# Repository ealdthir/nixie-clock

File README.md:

View this project on [CADLAB.io](https://cadlab.io/project/1190). 

# nixie-clock

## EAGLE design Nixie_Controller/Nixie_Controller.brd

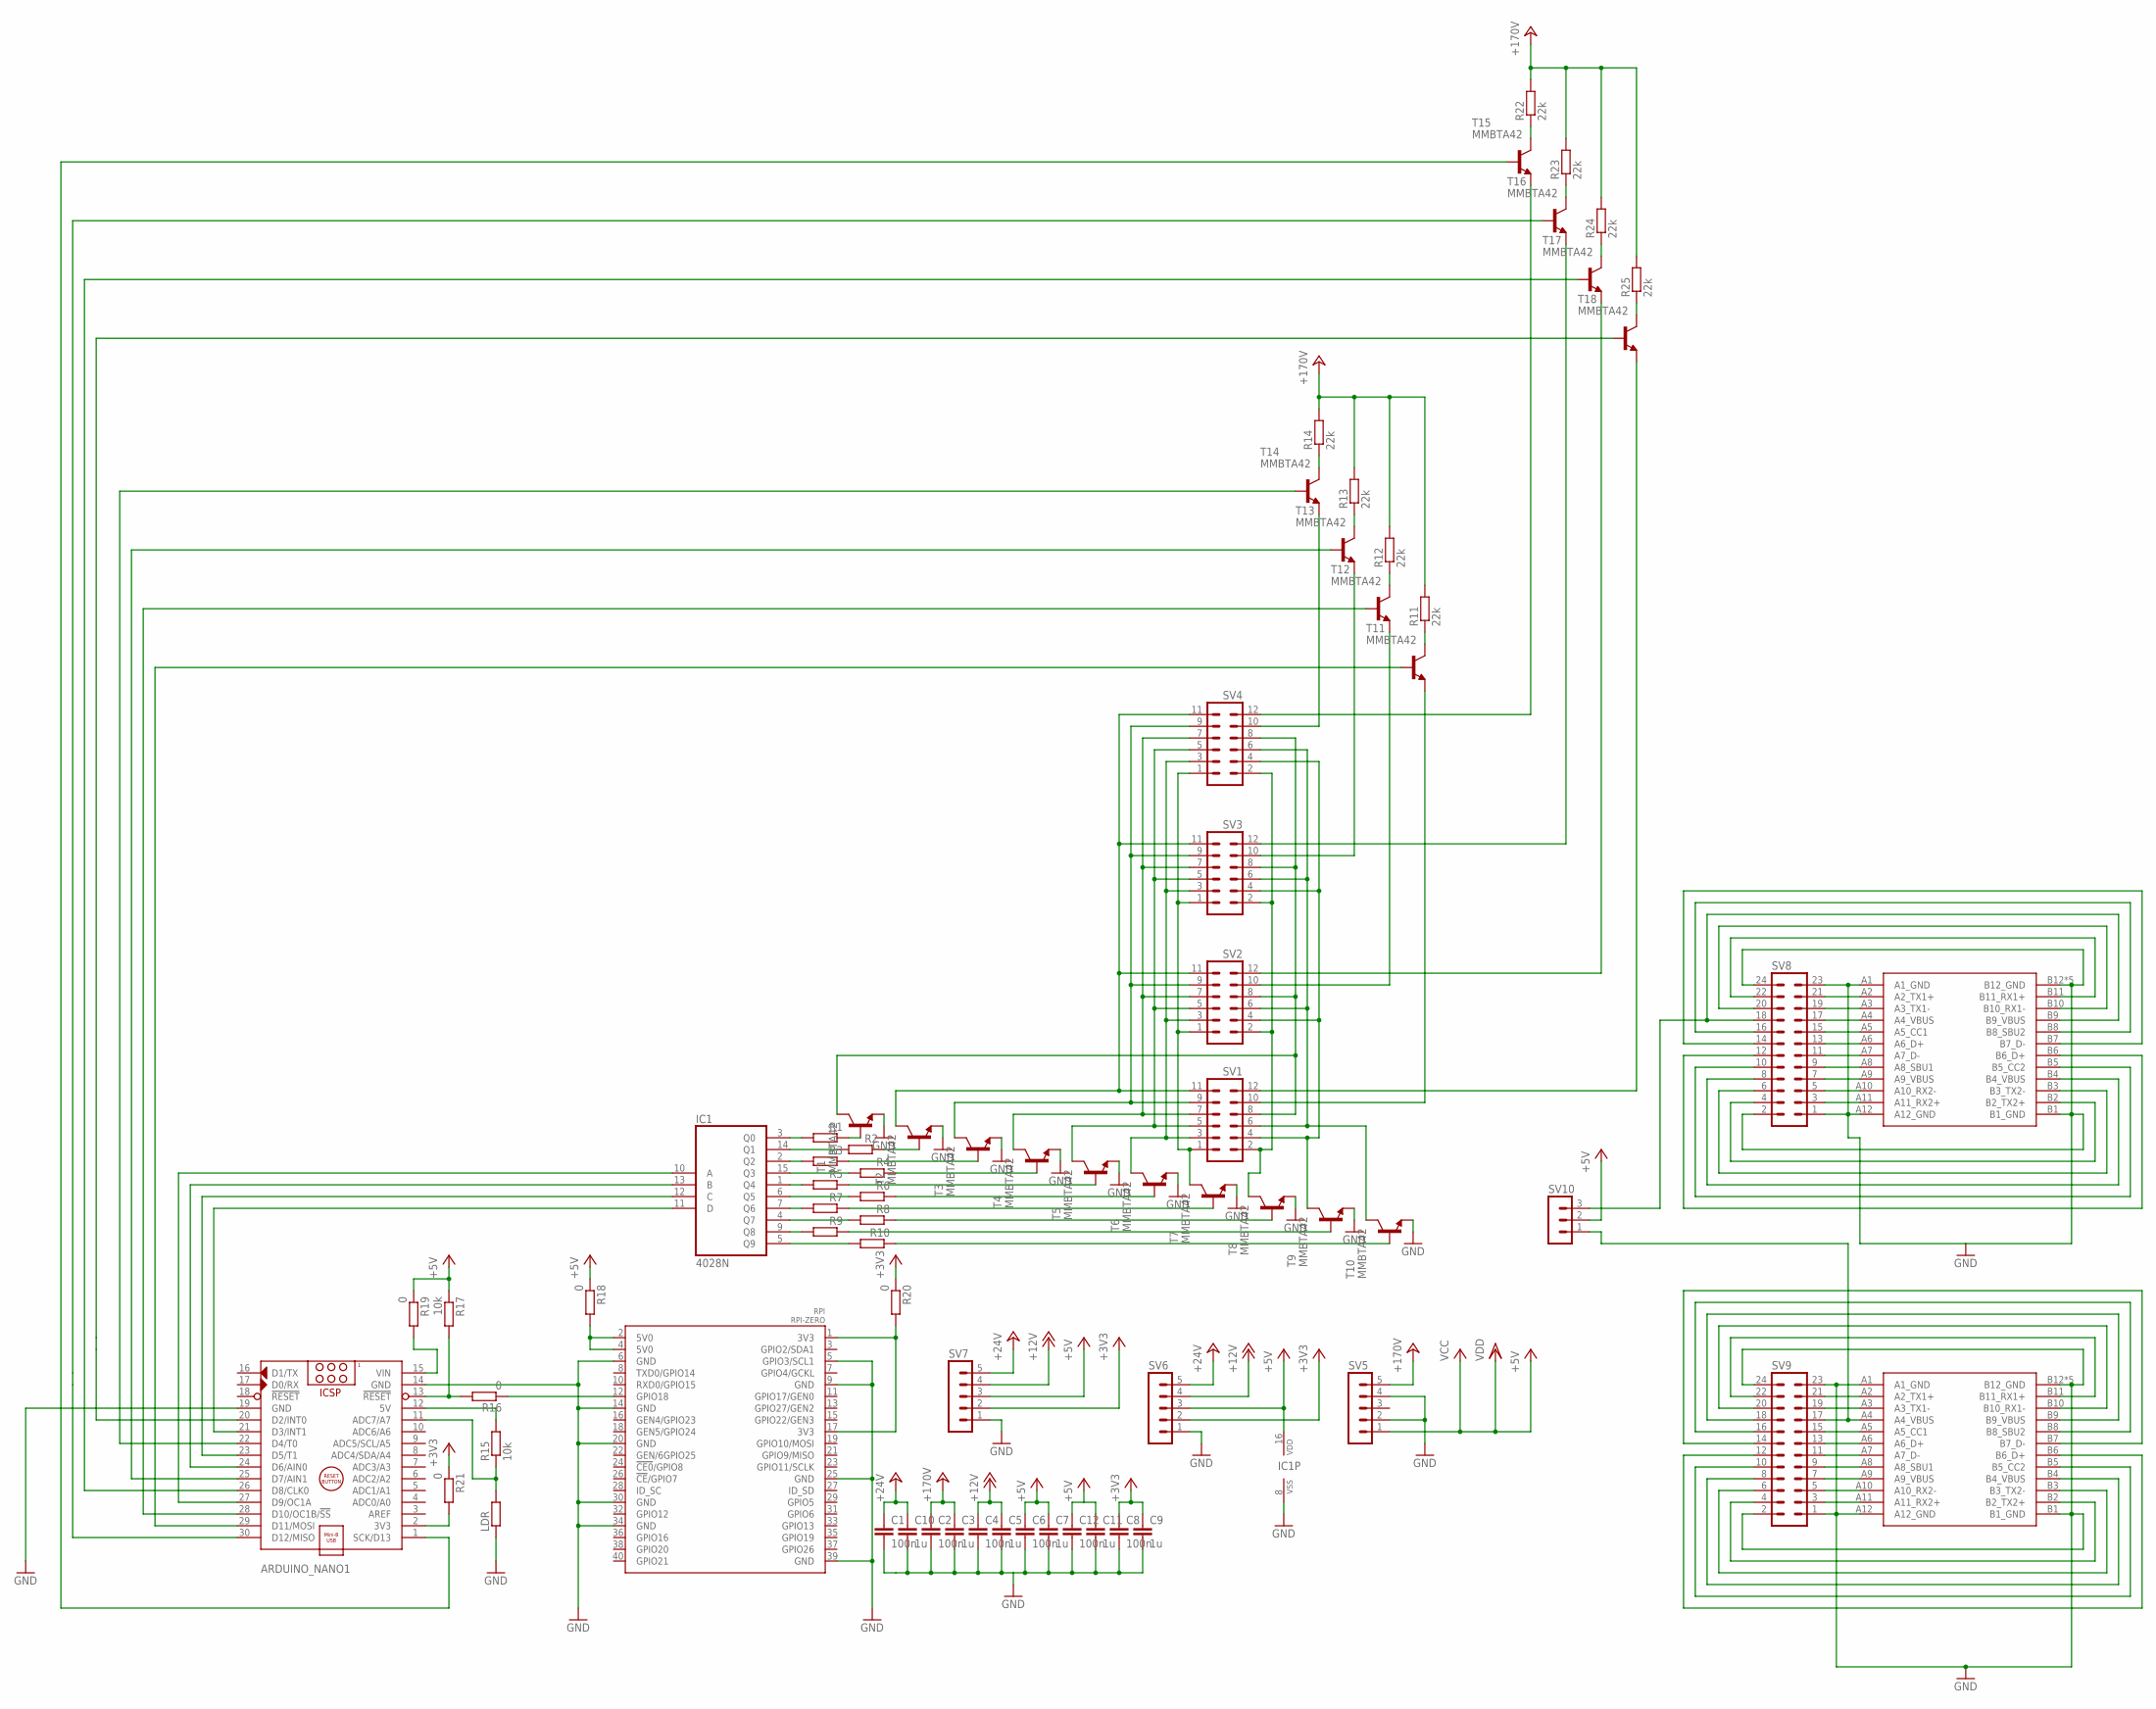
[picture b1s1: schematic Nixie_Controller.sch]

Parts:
ARDUINO_NANO1: ARDUINO_NANO
C1, C2, C4, C6, C8, C12: 100n; C0805
C3, C5, C7, C9, C10, C11: 1u; C0805
IC1: 4028N; DIL16
LDR: R-EU_0204/7; 0204/7
R1, R2, R3, R4, R5, R6, R7, R8, R9, R10: R-EU_R0603; R0603
R11, R12, R13, R14, R22, R23, R24, R25: 22k; R0603
R15, R17: 10k; R0603
R16, R18, R19, R20, R21: 0; R0603
RPI: RPI-ZERO; RASP_PI_ZERO_BOARD_FULL
SV1, SV2, SV3, SV4: MA06-2
SV5, SV6, SV7: MA05-1
SV8, SV9: MA12-2
SV10: MA03-1
T1, T2, T3, T4, T5, T6, T7, T8, T9, T10, T11, T12, T13, T14, T15, T16, T17, T18: MMBTA42; SOT23
USBC1, USBC2: USB-TYPE-C

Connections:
3V3@2: R20.2, RPI.1 (3V3), RPI.17 (3V3)
+3V3: C8.1, C9.1, R20.1, R21.1, SV6.2, SV7.2
+5V: R18.2, RPI.2 (5V0), RPI.4 (5V0)
+12V: C4.1, C5.1, SV6.4, SV7.4
+24V: C1.1, C10.1, SV6.5, SV7.5
+170V: C2.1, C3.1, R11.2, R12.2, R13.2, R14.2, R22.2, R23.2, R24.2, R25.2, SV5.5
GND: ARDUINO_NANO1.14 (GND), ARDUINO_NANO1.19 (GND), C1.2, C2.2, C3.2, C4.2, C5.2, C6.2, C7.2, C8.2, C9.2, C10.2, C11.2, C12.2, IC1.8 (VSS), LDR.1, RPI.5 (GPIO3/SCL1), RPI.6 (GND), RPI.9 (GND), RPI.14 (GND), RPI.20 (GND), RPI.25 (GND), RPI.30 (GND), RPI.34 (GND), RPI.39 (GND), SV5.2, SV5.4, SV6.1, SV7.1, SV8.1, SV8.2, SV8.23, SV8.24, SV9.1, SV9.2, SV9.23, SV9.24, T1.2 (E), T2.2 (E), T3.2 (E), T4.2 (E), T5.2 (E), T6.2 (E), T7.2 (E), T8.2 (E), T9.2 (E), T10.2 (E), USBC1.A1 (A1_GND), USBC1.A12 (A12_GND), USBC1.B1 (B1_GND), USBC1.B12 (B12_GND), USBC1.C1 (B12_GND), USBC1.C2 (B12_GND), USBC1.C3 (B12_GND), USBC1.C4 (B12_GND), USBC2.A1 (A1_GND), USBC2.A12 (A12_GND), USBC2.B1 (B1_GND), USBC2.B12 (B12_GND), USBC2.C1 (B12_GND), USBC2.C2 (B12_GND), USBC2.C3 (B12_GND), USBC2.C4 (B12_GND)
unnamed: IC1.3 (Q0), R1.2
unnamed: IC1.14 (Q1), R2.2
unnamed: IC1.2 (Q2), R3.2
unnamed: IC1.15 (Q3), R4.2
unnamed: IC1.1 (Q4), R5.2
unnamed: IC1.6 (Q5), R6.2
unnamed: IC1.7 (Q6), R7.2
unnamed: IC1.4 (Q7), R8.2
unnamed: IC1.9 (Q8), R9.2
unnamed: IC1.5 (Q9), R10.2
unnamed: R1.1, T1.1 (B)
unnamed: R2.1, T2.1 (B)
unnamed: R3.1, T3.1 (B)
unnamed: R4.1, T4.1 (B)
unnamed: R6.1, T6.1 (B)
unnamed: R5.1, T5.1 (B)
unnamed: R7.1, T7.1 (B)
unnamed: R8.1, T8.1 (B)
unnamed: R10.1, T10.1 (B)
unnamed: R9.1, T9.1 (B)
unnamed: SV1.11, SV2.11, SV3.11, SV4.11, T2.3 (C)
unnamed: SV1.9, SV2.9, SV3.9, SV4.9, T3.3 (C)
unnamed: SV1.7, SV2.7, SV3.7, SV4.7, T4.3 (C)
unnamed: SV1.5, SV2.5, SV3.5, SV4.5, T5.3 (C)
unnamed: SV1.3, SV2.3, SV3.3, SV4.3, T6.3 (C)
unnamed: SV1.1, SV2.1, SV3.1, SV4.1, T7.3 (C)
unnamed: SV1.2, SV2.2, SV3.2, SV4.2, T8.3 (C)
unnamed: SV1.4, SV2.4, SV3.4, SV4.4, T9.3 (C)
unnamed: SV1.6, SV2.6, SV3.6, SV4.6, T10.3 (C)
unnamed: SV1.8, SV2.8, SV3.8, SV4.8, T1.3 (C)
unnamed: R14.1, T14.3 (C)
unnamed: R11.1, T11.3 (C)
unnamed: R12.1, T12.3 (C)
unnamed: R13.1, T13.3 (C)
unnamed: SV4.10, T14.2 (E)
unnamed: SV3.10, T13.2 (E)
unnamed: SV2.10, T12.2 (E)
unnamed: SV1.10, T11.2 (E)
unnamed: ARDUINO_NANO1.2 (3V3), R21.2
unnamed: ARDUINO_NANO1.28 (D10/OC1B/!SS), T12.1 (B)
unnamed: SV8.21, USBC2.A2 (A2_TX1+)
unnamed: SV8.19, USBC2.A3 (A3_TX1-)
unnamed: ARDUINO_NANO1.13 (!RESET), R16.2, R17.2
unnamed: ARDUINO_NANO1.12 (5V), R15.2
unnamed: ARDUINO_NANO1.11 (ADC7/A7), LDR.2, R15.1
unnamed: ARDUINO_NANO1.29 (D11/MOSI), T11.1 (B)
unnamed: SV8.17, USBC2.A4 (A4_VBUS)
unnamed: ARDUINO_NANO1.25 (D7/AIN1), T13.1 (B)
unnamed: ARDUINO_NANO1.22 (D4/T0), T14.1 (B)
unnamed: SV8.15, USBC2.A5 (A5_CC1)
unnamed: SV8.13, USBC2.A6 (A6_D+)
unnamed: SV8.11, USBC2.A7 (A7_D-)
unnamed: SV8.9, USBC2.A8 (A8_SBU1)
unnamed: SV8.7, USBC2.A9 (A9_VBUS)
unnamed: SV8.5, USBC2.A10 (A10_RX2-)
unnamed: SV8.3, USBC2.A11 (A11_RX2+)
unnamed: R22.1, T15.3 (C)
unnamed: R25.1, T18.3 (C)
unnamed: SV9.21, USBC1.A2 (A2_TX1+)
unnamed: SV9.19, USBC1.A3 (A3_TX1-)
unnamed: SV9.17, SV10.1, USBC1.A4 (A4_VBUS)
unnamed: SV9.15, USBC1.A5 (A5_CC1)
unnamed: SV9.13, USBC1.A6 (A6_D+)
unnamed: SV9.11, USBC1.A7 (A7_D-)
unnamed: SV9.9, USBC1.A8 (A8_SBU1)
unnamed: SV9.7, USBC1.A9 (A9_VBUS)
unnamed: SV9.5, USBC1.A10 (A10_RX2-)
unnamed: SV9.3, USBC1.A11 (A11_RX2+)
unnamed: R24.1, T17.3 (C)
unnamed: R23.1, T16.3 (C)
unnamed: SV9.4, USBC1.B2 (B2_TX2+)
unnamed: SV9.6, USBC1.B3 (B3_TX2-)
unnamed: SV9.8, USBC1.B4 (B4_VBUS)
unnamed: SV9.10, USBC1.B5 (B5_CC2)
unnamed: SV9.12, USBC1.B6 (B6_D+)
unnamed: SV4.12, T15.2 (E)
unnamed: SV9.22, USBC1.B11 (B11_RX1+)
unnamed: SV9.20, USBC1.B10 (B10_RX1-)
unnamed: SV9.18, USBC1.B9 (B9_VBUS)
unnamed: SV9.16, USBC1.B8 (B8_SBU2)
unnamed: SV9.14, USBC1.B7 (B7_D-)
unnamed: SV3.12, T16.2 (E)
unnamed: SV8.4, USBC2.B2 (B2_TX2+)
unnamed: SV8.6, USBC2.B3 (B3_TX2-)
unnamed: SV8.8, USBC2.B4 (B4_VBUS)
unnamed: SV8.10, USBC2.B5 (B5_CC2)
unnamed: SV8.12, USBC2.B6 (B6_D+)
unnamed: SV2.12, T17.2 (E)
unnamed: SV8.22, USBC2.B11 (B11_RX1+)
unnamed: SV8.20, USBC2.B10 (B10_RX1-)
unnamed: SV8.18, SV10.3, USBC2.B9 (B9_VBUS)
unnamed: SV8.16, USBC2.B8 (B8_SBU2)
unnamed: SV8.14, USBC2.B7 (B7_D-)
unnamed: R16.1, RPI.12 (GPIO18)
unnamed: SV1.12, T18.2 (E)
unnamed: ARDUINO_NANO1.15 (VIN), R19.2
unnamed: ARDUINO_NANO1.1 (SCK/D13), T15.1 (B)
unnamed: ARDUINO_NANO1.20 (D2/INT0), T18.1 (B)
unnamed: ARDUINO_NANO1.26 (D8/CLK0), T17.1 (B)
unnamed: ARDUINO_NANO1.30 (D12/MISO), T16.1 (B)
unnamed: ARDUINO_NANO1.21 (D3/INT1), IC1.11 (D)
unnamed: ARDUINO_NANO1.23 (D5/T1), IC1.12 (C)
unnamed: ARDUINO_NANO1.24 (D6/AIN0), IC1.13 (B)
unnamed: ARDUINO_NANO1.27 (D9/OC1A), IC1.10 (A)
VDD: C6.1, C7.1, C11.1, C12.1, IC1.16 (VDD), R17.1, R18.1, R19.1, SV5.1, SV6.3, SV7.3, SV10.2

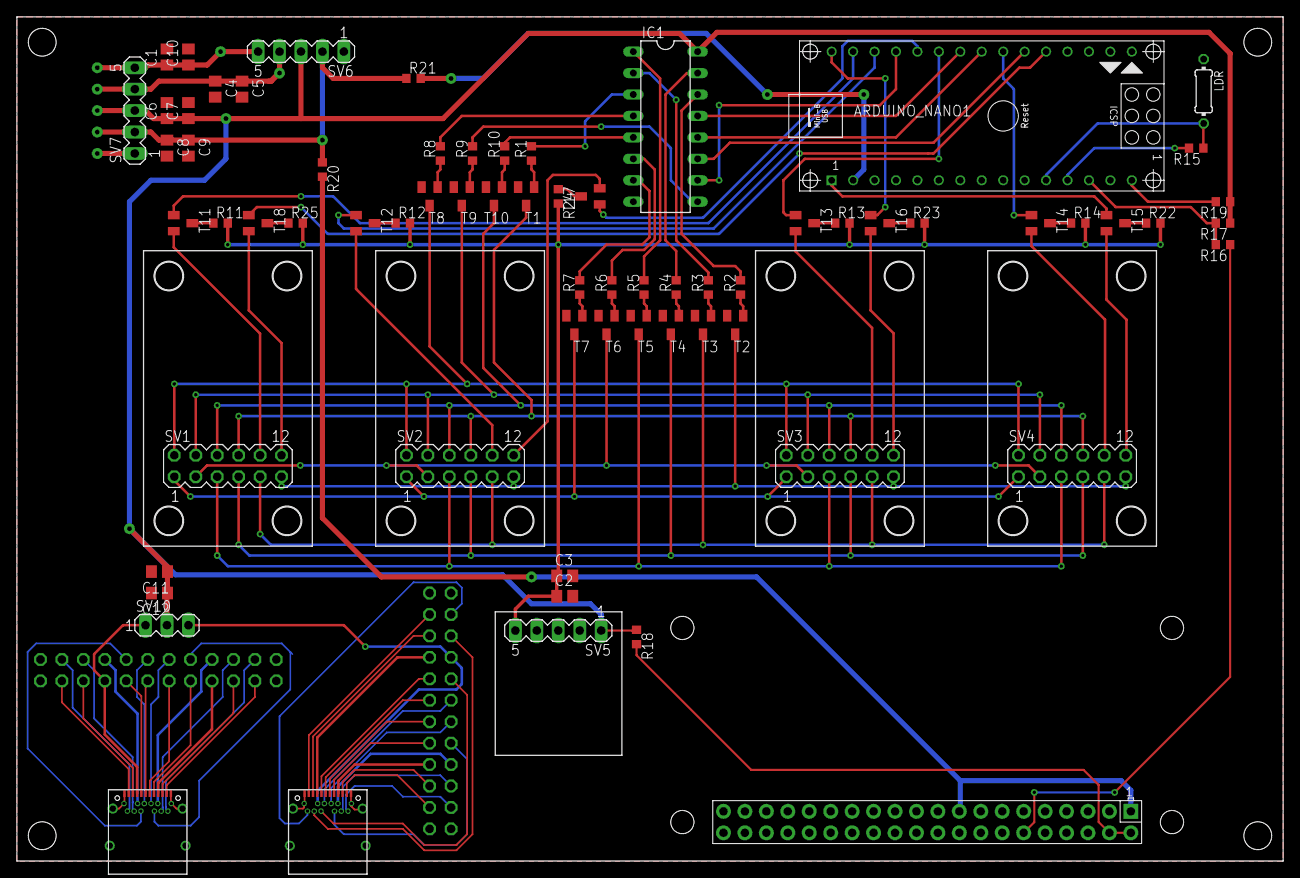
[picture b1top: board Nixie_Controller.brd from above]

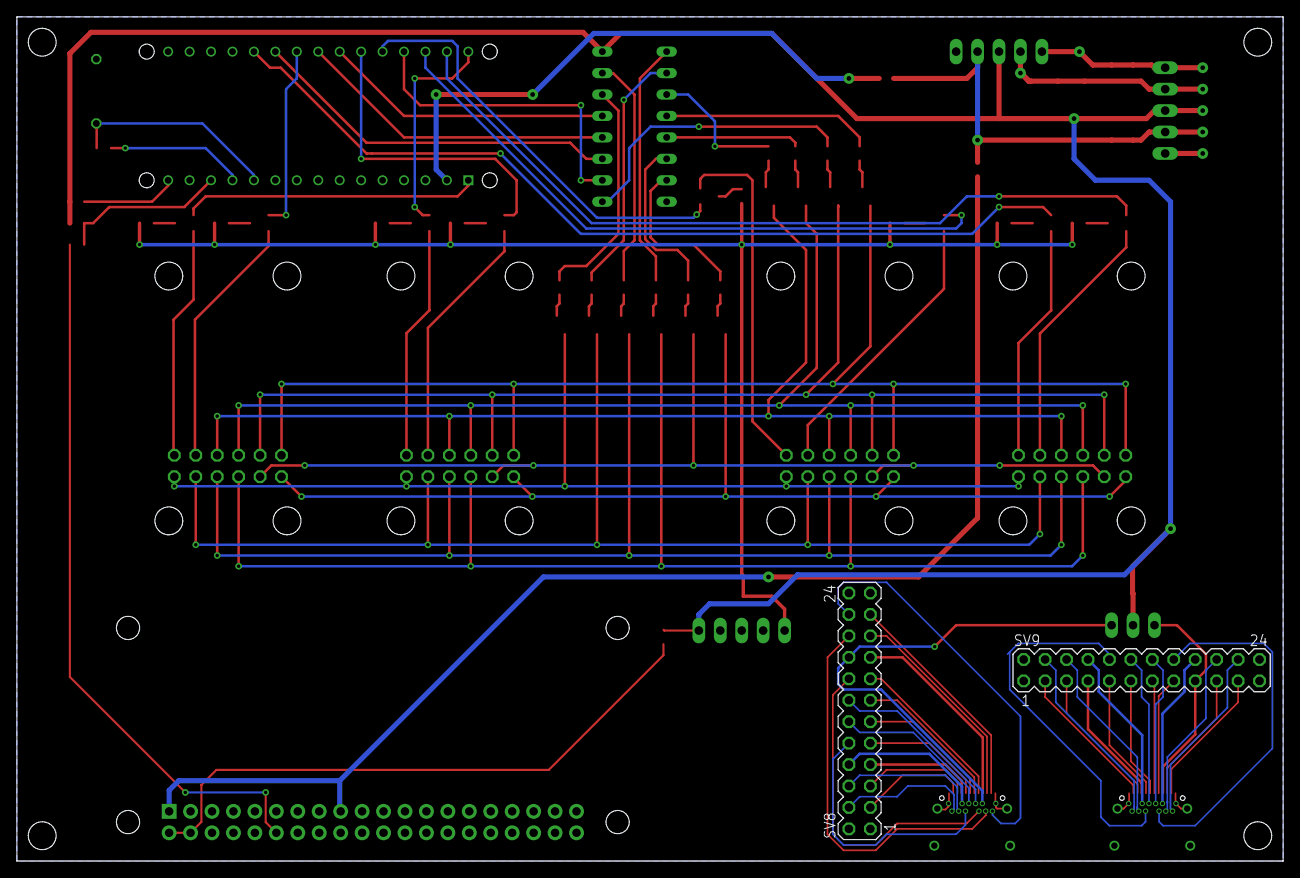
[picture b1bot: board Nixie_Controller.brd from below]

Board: 2 copper layers, 150.0 x 100.0 mm, 71 parts (2 on the bottom side), 112 nets.

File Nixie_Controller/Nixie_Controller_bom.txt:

Stückliste exportiert aus C:/Users/Yannick/Documents/eagle/nixie-clock/Nixie_Controller/Nixie_Controller.sch am 29.06.2018 16:21

Qty Value      Device       Package                 Parts                                                                           Description                MF MPN OC_FARNELL OC_NEWARK
1              ARDUINO_NANO ARDUINO_NANO            ARDUINO_NANO1                                                                   Arduino Nano V3.0 Module                              
1              MA03-1       MA03-1                  SV10                                                                            PIN HEADER                        unknown    unknown  
3              MA05-1       MA05-1                  SV5, SV6, SV7                                                                   PIN HEADER                        unknown    unknown  
4              MA06-2       MA06-2                  SV1, SV2, SV3, SV4                                                              PIN HEADER                        unknown    unknown  
2              MA12-2       MA12-2                  SV8, SV9                                                                        PIN HEADER                        unknown    unknown  
1              R-EU_0204/7  0204/7                  LDR                                                                             RESISTOR, European symbol                             
10             R-EU_R0603   R0603                   R1, R2, R3, R4, R5, R6, R7, R8, R9, R10                                         RESISTOR, European symbol                             
5   0          R-EU_R0603   R0603                   R16, R18, R19, R20, R21                                                         RESISTOR, European symbol                             
5   100n       C-EUC0805    C0805                   C1, C2, C4, C6, C8                                                              CAPACITOR, European symbol                            
2   10k        R-EU_R0603   R0603                   R15, R17                                                                        RESISTOR, European symbol                             
5   1u         C-EUC0805    C0805                   C3, C5, C7, C9, C10                                                             CAPACITOR, European symbol                            
8   22k        R-EU_R0603   R0603                   R11, R12, R13, R14, R22, R23, R24, R25                                          RESISTOR, European symbol                             
1   4028N      4028N        DIL16                   IC1                                                                             BCD to decimal DECODER                                
18  MMBTA42    BC850        SOT23                   T1, T2, T3, T4, T5, T6, T7, T8, T9, T10, T11, T12, T13, T14, T15, T16, T17, T18 NPN TRANSISTOR                                        
1   RPI-ZERO   RPI-ZERO     RASP_PI_ZERO_BOARD_FULL RPI                                                                                                                                   
2   USB-TYPE-C USB-TYPE-C   USB-TYPE-C              USBC1, USBC2

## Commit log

2018-06-20 feat: add all files
2018-06-20 chore: improve folder structure
    move all files for the nixie adapter board to the Nixie_board folder
    rename the Nixie Controller folder to Nixie_Board
2018-06-20 feat: add license
    Add the LICENSE file
2018-06-20 fix: add zero ohms to supplies
    Add a zero ohm resistor between the Arduino 3.3V and the 3.3V supply voltage.
    Add a zero ohm resistor between the raspberry pi 5V and 3.3V and their respective supply voltages.
    Remove the second connection to the arduino reset, because they are internally connected
2018-06-21 fix: add resistors from schematic fix
    Add the three 0 ohm resistors to the board, which were added in the schematic fix
2018-06-21 fix: reroute multiple wires
    Rerouted multiple wires and moved a few components, mainly for aesthetic reasons
2018-06-21 Backlink to CADLAB.io has been added.
2018-06-25 fix: add supply vias
    Add a few vias to the supply connections, to be able to solder additional wires to the supply connections if needed
    Reroute a few traces
2018-06-29 chore: auto fix
    Upload an automatic change to the .epf file
2018-06-29 feat: Add double anode nixie support
    Add support for nixie tubes that use two anodes.
2018-06-29 fix: Remove DRC errors
    Remove the erros the DRC mentioned.
    Reroute and move multiple components for a cleaner look.
2018-06-29 fix: Reroute
    Reroute multiple connections for cleaner looks.
2018-06-29 feat: Add bom
    Add a bill of materials file
2018-06-29 fix: Change names
    Change the names of the Raspberry Pi and the USB-C connectors to something more meaningfull.
2018-06-29 fix: Update .epf to new Eagle
    Update the .epf file to Version 09.00.01
2018-07-01 fix: Reroute traces
    Reroute multiple traces for a cleaner look.
    Increase the tracewidth of the USB VBUS Signal.
    Add decoupling capacitors to the USB supply.
2018-07-07 feat: Generate Gerberfiles
